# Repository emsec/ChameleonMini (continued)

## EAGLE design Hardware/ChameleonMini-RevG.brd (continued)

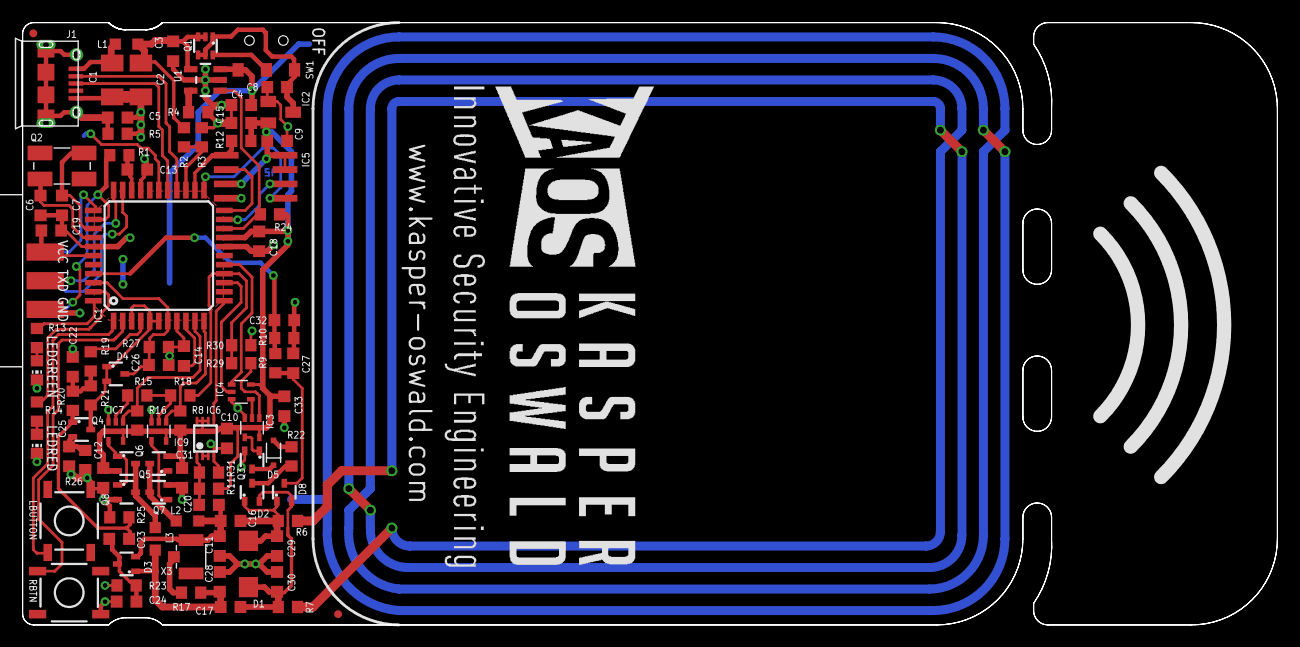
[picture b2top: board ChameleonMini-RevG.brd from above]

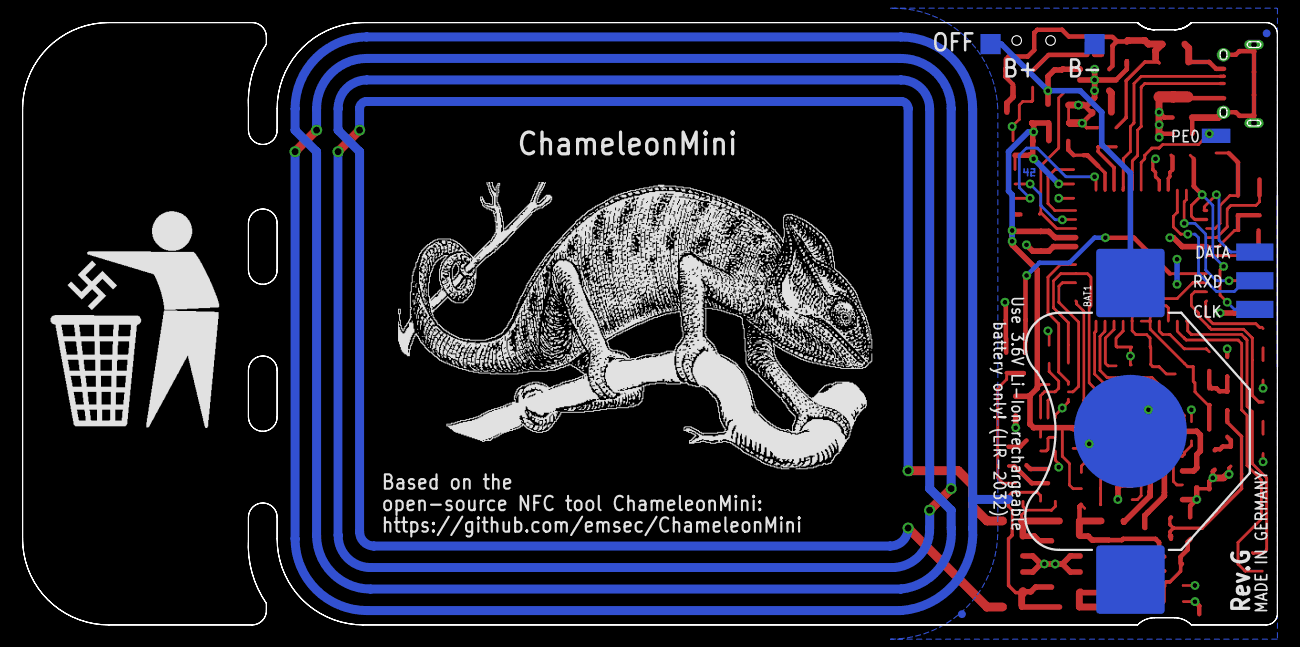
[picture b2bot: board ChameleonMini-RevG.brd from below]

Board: 2 copper layers, 111.1 x 53.3 mm, 104 parts (6 on the bottom side), 64 nets.

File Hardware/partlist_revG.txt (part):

Partlist

Exported from ChameleonMini-RevG.sch at 07.10.2016 23:09:59

EAGLE Version 6.6.0 Copyright (c) 1988-2014 CadSoft

Assembly variant: 

Part     Value            Device                  Package             Library                    Sheet

B+       TPTP18SQ         TPTP18SQ                TP18SQ              testpad                    1
B-       TPTP18SQ         TPTP18SQ                TP18SQ              testpad                    1
BAT1     3002             3002                    BATTCON_20MM        Keystone-3002              1
C1       10n              C-EUC1206K              C1206K              rcl                        1
C2       10n              C-EUC1206K              C1206K              rcl                        1
C3       4u7              C-EUC0603K              C0603K              rcl                        1
C4       4u7/10V/X5R      C-EUC0603K              C0603K              rcl                        1
C5       10n              C-EUC0603K              C0603K              rcl                        1
C6       22p              C-EUC0603K              C0603K              rcl                        1
C7       22p              C-EUC0603K              C0603K              rcl                        1
C8       4u7              C-EUC0603K              C0603K              rcl                        1
C9       4u7              C-EUC0603K              C0603K              rcl                        1
C10      100n             C-EUC0603K              C0603K              rcl                        1
C11      150p             C-EUC0603K              C0603K              rcl                        2
C12      100n             C-EUC0603K              C0603K              rcl                        2
C13      100n             C-EUC0603K              C0603K              rcl                        1
C14      100n             C-EUC0603K              C0603K              rcl                        1
C15      100n             C-EUC0603K              C0603K              rcl                        1
C16      100p             C-EUC0603K              C0603K              rcl                        2
C17      100p             C-EUC0603K              C0603K              rcl                        2
C18      100n             C-EUC0603K              C0603K              rcl                        1
C19      100n             C-EUC0603K              C0603K              rcl                        1
C20      150p/NP0         C-EUC0603K              C0603K              rcl                        2
C22      100n             C-EUC0603K              C0603K              rcl                        2
C23      1n               C-EUC0603K              C0603K              rcl                        2
C24      22p              C-EUC0603K              C0603K              rcl                        2
C25      22p              C-EUC0603K              C0603K              rcl                        2
C26      22p              C-EUC0603K              C0603K              rcl                        2
C27      22p              C-EUC0603K              C0603K              rcl                        2
C28      150p             C-EUC0603K              C0603K              rcl                        2
C29      N.M.             C-EUC0603K              C0603K              rcl                        2
C30      N.M.             C-EUC0603K              C0603K              rcl                        2
C31      100n             C-EUC0603K              C0603K              rcl                        2
C32      100n             C-EUC0603K              C0603K              rcl                        2
C33      100n             C-EUC0603K              C0603K              rcl                        1
D1       N.M.             SMAJ                    DO214AC             Suppressor                 2
D2       BAS70-05W        BAS70-05W               SOT323              NXP-Diode                  2
D3       BAS70-05W        BAS70-05W               SOT323              NXP-Diode                  2
D4       BAS70-05W        BAS70-05W               SOT323              NXP-Diode                  2
D5       Schottky         1PS76SB70               SOD323(F)           nxp_60                     2
D8       BAS70-05W        BAS70-05W               SOT323              NXP-Diode                  2
IC1      ATxmega128A4U-AU ATXMEGA_A4-A            TQFP44              _ATxmega                   1
IC2      MCP1700          MCP1702                 SOT23               Microchip-MCP1702          1
IC3      7408             74LVC1G08DCK            SC70-5              74xx-little-de             1
IC4      7486             74AHC1G86DCK            SC70-5              74xx-little-de             1
IC5      MB85RS256        MB85RS                  SO-08               Fujitsu-FRAM               1
IC6      7474             74LVC1G74DC             VSSOP8              74LVC1G74                  2
IC7      7432             74AHC1G32DCK            SC70-5              74xx-little-de             2
IC9      7432             74AHC1G32DCK            SC70-5              74xx-little-de             2
J1       Micro USB        USB-MICROB-2            USB-MICROB-10118194 we-con                     1
L1       33R@100MHz       L-EUL2012C              L2012C              rcl                        1
L2       270n             L-EUL2012C              L2012C              rcl                        2
L3       270n             L-EUL2012C              L2012C              rcl                        2
LBUTTON                   SWITCH_SPST_4_PINSQUARE TACTILE-SWITCH-SMD  SparkFun-Electromechanical 1
LEDGREEN HSMG-C190        LED-0603                CHIPLED-0603        led                        1
LEDRED   HSMS-C190        LED-0603                CHIPLED-0603        led                        1
PE0      PAD              WIREPADSMD1,27-254      SMD1,27-2,54        wirepad                    1
Q1       Si1967DH         BSS84AKS                SOT363              NXP-MOS                    1
Q2       13.56 MHz        TXC7B                   5MMX3.2MM           TXC-Crystal                1
Q3       BSS138           BSS138BKW               SOT323              NXP-MOS                    2
Q4       BC846W           BC84XW                  SOT323              NXP-BJT                    2
Q5       BSS84            BSS84AKW                SOT323              NXP-MOS                    2
Q6       BSS84            BSS84AKW                SOT323              NXP-MOS                    2
Q7       BSS138           BSS138BKW               SOT323              NXP-MOS                    2
Q8       BSS138           BSS138BKW               SOT323              NXP-MOS                    2
R1       10k              R-EU_R0603              R0603               rcl                        1
R2       4k7              R-EU_R0603              R0603               rcl                        1
R3       10k              R-EU_R0603              R0603               rcl                        1
R4       47k              R-EU_R0603              R0603               rcl                        1
R5       1Meg             R-EU_R0603              R0603               rcl                        1
R6       3R3              R-EU_R0603              R0603               rcl                        2
R7       3R3              R-EU_R0603              R0603               rcl                        2
R8       100k             R-EU_R0603              R0603               rcl                        2
R9       47k              R-EU_R0603              R0603               rcl                        2
R10      1k               R-EU_R0603              R0603               rcl                        2
R11      10k              R-EU_R0603              R0603               rcl                        2
R12      100k             R-EU_R0603              R0603               rcl                        1
R13      220R             R-EU_R0603              R0603               rcl                        1
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
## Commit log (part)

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2018-09-12 added LATEST firmware
2018-10-17 Buildable, ISR sharing
2018-10-28 Update Sl2s2002.c
    option bit also for sending security state in single read
2018-11-10 Added all response error codes from the standard
2018-11-10 Checked with a real tag and the error is correct. Also fixed a small error which let the tag still go out of bound.
2018-11-10 Fu..ed up a define with commit 288f6721b10299548e6a4cdd34017535f9e0b542
2018-11-10 Modified ISO15692-A.h CompareUid, temporary fix to Sl2s2002.c and Vicinity.c
2018-11-12 TITagitstandardFlipUid refactored
2018-11-22 ISO15693_MIN_FRAME_SIZE for iso15 should be 4
2018-11-29 Removed testing stuff and removed todo
2018-12-03 Update Settings.c
    Individual Config for LED & Button now working -> Fixed.
2018-12-04 Added Configurability for global or individual settings of LEDs, Buttons and Logging. New command "USER_INTERFACE", Parameters "GLOBAL", "INDIVIDUAL" Feature can be enabled in Makefile by enabling "S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
2018-12-04 Fixed nasty bug in ISO15693PrepareFrame, removed unnecessary includes and implemented failsafe to command not supported to fix problems with Android apps. Everything just works.
2018-12-10 EM4233 first draft
2018-12-14 Added EM4233 example dump and bug fixes
2018-12-17 Added fake login command
2018-12-18 Modified EM4233_STD_MEM_SIZE to reflect real tag size
2018-12-19 Indentation fixes
2018-12-25 Resetting LoadModState to avoid erratic behaviour
2018-12-26 Removed old LockBit masks and updated a couple of commands to mimick real tag behaviour
2018-12-27 First draft of anticollision sequence
    Only 1 slot mode has been implemented, but it seems to work even for 16 slots mode. This needs to be checked with other readers.
2018-12-28 Stupid me introduced a bug in Write_Single
2019-01-15 Add: LED Blink when clone done
2019-03-05 Added stub EM mutual auth commands and fixed a couple of bugs
    E0 and E1 commands will be expanded as reverse engineering continues. At the moment E0 will be used to work on reader response to A1 random number.
    Fixed 2 different bugs in Login. Fixed Lock DSFID command
    Removed frame integrity checks from PrepareFrame, since it's already needed to do them before PrepareFrame should be called
2019-03-21 fixed bug with volatile position
2019-03-21 fixed bugs with status ID and return on end of non-void function
2019-08-16 Add Mifare Mini support
2019-08-25 Add MFDetection support
2019-09-17 fixed indentation
2019-11-07 Modified Reader14443A to only use configured card types
    This allows the Reader14443A.c file to be compiled successfully when
    the support for some card types is disabled in the Makefile
2019-11-15 run make style #237
2019-11-24 Add mfu clone function
2019-11-25 Docs: add documentation for CLONE_MFU button and command actions
2019-12-08 Faster ISR sharing in ASM
    While in the process of writing a new codec I stumbled upon the long
    standing issue of ISR sharing in AVR MCUs.
    Actually this is accomplished with an ISR written in C, which simply
    calls another plain C function referenced via a function pointer
    updated at runtime.
    This approach is slow because GCC can't optimize the ISR, since it
2019-12-22 jsdelivr.net → githack.com (for HTML files)
2019-12-28 Updated Readme.txt to MD and added Linux build instructions
2019-12-31 Added instructions for Linux
2020-01-02 migrate all links to statically.io
2020-01-13 added COMPATIBILITY_WRITE support, fixed some comments
2020-01-24 fix #254 update docs
2020-06-13 Fixed a typo in NTAG215.h
    Fixed the typo pointed out by @HexRabbit
2020-06-16 update NAK comment for NTAG
    (cherry picked from commit 928cc10bcd09c008d80a2e9c499289d0cb8568de)
2020-06-16 Added empty dump example for NTAG215
    (cherry picked from commit 61e455bfb47fbe93ec38ec7d112e01c976976190)
2020-09-01 pin command initial version
2020-09-03 Improved ISO15693 applications performance
    Removed the if-elseif in EM4233 to use a switch case which yields minor
    speed improvements of ~1,5 microseconds
    Avoid reading the UID every AppProcess tick in both EM4233 and TiTagIT
    to save ~11 microseconds.
2020-09-10 Fixed timing issues with Read Multiple Blocks
    ISO15693 CRC calculation is slow and it delayed too much transmission of long
    frames. Some readers marked transmission as unsuccesfull and ignored data.
    Moving CRC calculation inside the codec allows to start modulating the field
    while the CRC is not yet ready but, by the time it has to be trasmitted,
    calculation will be done.
    This fixes https://github.com/emsec/ChameleonMini/issues/262
2020-09-28 make style, update Latest
2020-10-14 Working in windows under cygwin
2020-10-17 Adding updated and new support for DES and AES-128 encryption with HW accelertion
2020-10-17 Adding the DESFire tag emulation docs file
2020-10-17 Placing the main source files for the DESFire tag support into Application
2020-10-18 A few fixes and loose ends
2020-10-18 Fixing logging issue where if starting from a logmode different from LIVE with -DLOG_SETTING_GLOBAL set in the Makefile, the active configuration does not respond to LOGMODE=LIVE.
2020-10-23 update docs, remove Latest folder
2021-04-09 Add implementation of TI Tagit Plus vicinity card. Remove unapparent configuration dependency on CONFIG_ISO15693_SNIFF_SUPPORT for vicinity card applications to compile by extending criteria when to 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
2021-10-14 Firmware support for Chameleon Tiny
    This adds support for Proxgrind's Chameleon Tiny (Pro) hardware features which
    consist in having more LEDs (one per slot) and having an uart interface that
    is wired to a bluetooth module that allows wireless communication to the
    device with an Android app.
    Support for these features can be enabled by uncommenting the respective lines
    in the firmware Makefile that define CHAMELEON_TINY_SUPPORT and
2022-01-01 Partial progress: The Omnikey reader now offers a 9370 response that is not getting handled yet
2022-01-02 Incremental backup (still stuck in a loop after responding to the Omnikey's 9370...)
2022-01-14 removed deprecated ntag215 application
2022-01-16 Fixing a few details noted in #302
2022-01-16 Fix the issue with the UID0 byte of a random UID needing to be 0x08 noted in the #302 discussion
2022-01-18 Progress towards #313 ... Needs further testing
2022-01-20 Fixing issue with trailing CRCA missing from #313
2022-01-21 Most of the stuff should be working, project folder cleaned a bit
2022-01-21 Fixing ISO-7816 wrapped commands -- CRC needs to be computed over entire buffer, including the prologue
2022-01-24 FAST_READ is now implemented correctly
2022-01-24 Cleaned comments, removed some TODOs
2022-01-27 Fixing commented multi-line macro in violation of the `make style` guidelines
2022-01-28 Ported fptrs fixes
2022-01-30 Re-implementing the 3DES crypto with CBC
2022-01-31 AuthLegacy(0x0A) works using 3DES enc/dec modes
2022-01-31 Calling AppProcess as suggested by @cacke-r
2022-01-31 add github action to build desfire fw
2022-01-31 Added undocumented commands by testing on real tags
2022-01-31 Fixed makefile to add ntag215 support after catching up to emsec master repo
2022-01-31 Stashing incremental testing release code
2022-02-05 Working AES128 auth and ISO auth ; Still need to debug the legacy auth
2022-02-12 Fixing bug where we must first auth with the legacy command mentioned in #313
2022-02-12 Making sure the auth AES and auth ISO handlers keep the chain of prior legacy auths intact
2022-02-12 Addressing the ACK/NAK keep-alive exchanges from some NXP readers noted by \@lvandenb in #313
2022-02-12 Finding other places to squeeze space for the DESFire config (Log and terminal buffers stored on the stack -- adding buffer full messages for INFO)
2022-02-12 Adding in preliminary AES transfer functions -- Trying to save space for more where it can be pruned -- III -- cf. #313
2022-02-12 Preliminary (partial) support for more CommModes -- This is going to need substantial testing
2022-02-13 Making a sane backup point while prfusely debugging
2022-02-13 Out of hell ... Everything seems to be working again with the MEMORY_LIMITED_TESTING define set in the Makefile :)
2022-02-14 *Should* finally be working now -- Problem was that the SETTINGS memory remapped the FLASH memory space used by avr-gcc\'s __flash to a custom .flashdata section after the LUFA build by a second call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
2022-02-23 Sniff15693: Implementation of Autocalibration command
2022-02-23 Add Autocalibrate command to chamtool
2022-02-23 Commands: Autocalibrate: Dont execute if ISO15693 codec uses autothreshold
2022-02-23 Sniff15693: Autocalibrate: Detect error case
    Detect the case, that we never receive a valid card frame.
    Restore original/recent threshold in this case.
2022-03-17 update Doxygen
2022-03-22 Adding more complete support for PM3 ISO auth (stashing incremental changes as reference point -- II)
2022-03-26 More progress towards PM3 compatible auth II
2022-03-30 Stashing more working code to test PM3 compatibility (ISO/EV1 auth)
2022-04-22 Incorporating bug fixes by @colinoflynn at https://github.com/colinoflynn/ChameleonMini/commits/desfire-fixes (see message in #313)
2022-05-13 Attempt to fix bug with `pm3 --> hf mfdes info` reported in #313
2022-06-02 Updates to make/build scripts ; Partial fixes to @colinoflynn\'s notes in #313 (success with \'hf mfdes info -- Still debugging auth exchanges)
2022-06-08 Fixing some make build script bugs
2022-06-15 ACR122U USB/PCSC reader stopped being responsive after all of the PM3 compat changes: Attempt to fix this problem (PM3 command support verified as still working) -- Cf. #313
2022-06-16 Cleaning up some old commented out macro definitions
2022-06-28 Updating source after the feedback from @fptrs in PR #319
2022-06-29 fix typos
2022-06-29 Updating the FLASH_DATA_ADDR value to the correct value for 6 slots (versus standard 8)
2022-06-29 Update Log.py
    change DESFire Generic Error decoder
2022-07-01 Several fixes to responsiveness and frozen behavior noted in PR #319
2022-07-15 Testing code updates with the PM3 -- a few small changes
2022-07-15 Saving work on the LibNFC testing code for DESFire builds
2022-07-17 New DF_ENCMODE command to set ECB/CBC crypto modes ; Incremental changes to LibNFC test code ; Incomplete docs to edit elsewhere
2022-07-17 Stashing working LibNFC test code -- ISO auth is working
2022-07-19 Updating TDEA (x3) crypto code to handle uneven buffer sizes ; Changes to DESFire auth instructions reinit / (in)validate state logic
2022-07-20 Multiple code cleanup changes to TransferState -- Enc of transfers is handled by the APDU pre/post process functions -- Restore point for previous functionality
2022-07-20 Current firmware builds tested with PM3 and LibNFC test code ; Still takes too long to verify the file mgmt and data manip programs
2022-07-20 fix github action name
2022-07-26 Cleaning up modifications used to test the development code
2022-07-26 Small changes to the NAK/ACK return size (4 bits versus 1 byte)
2022-10-14 Fix CMAC support for DESFire
2022-10-14 Decrypt encrypted payload for some DESFire EV1+ cases
2022-10-14 DESFire: Reclaim allocated space on PICC format
2022-10-14 Various debug messages + various fixes
2022-10-14 Fix command binary search
2022-10-14 DESFire: Various fixes
2022-10-16 Fix processing of native wrapped commands that have zeros as arguments
2022-10-18 Return correct error code when file index is out of range
2022-10-18 Set custom build name for Gallagher build
2022-11-13 Outline for loading Gallagher
2022-11-14 Minimal Gallagher self-programming support. Before testing on physical device.
2022-11-20 Split to functions, add terminal commands. Before testing.
2022-11-21 Remove some log messages
2023-04-24 Added dfu programmer 0.7.2
2023-04-25 Added download link for dgu prgorammer 0.7.2
2023-05-19 Move card specific info into the wiki
